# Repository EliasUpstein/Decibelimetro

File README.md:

# Decibelimetro
Proyecto anual integrador de la materia Medidas Electrónicas I - Ingeniería Electrónica - Universidad Tecnológica Nacional - Facultad Regional Buenos Aires

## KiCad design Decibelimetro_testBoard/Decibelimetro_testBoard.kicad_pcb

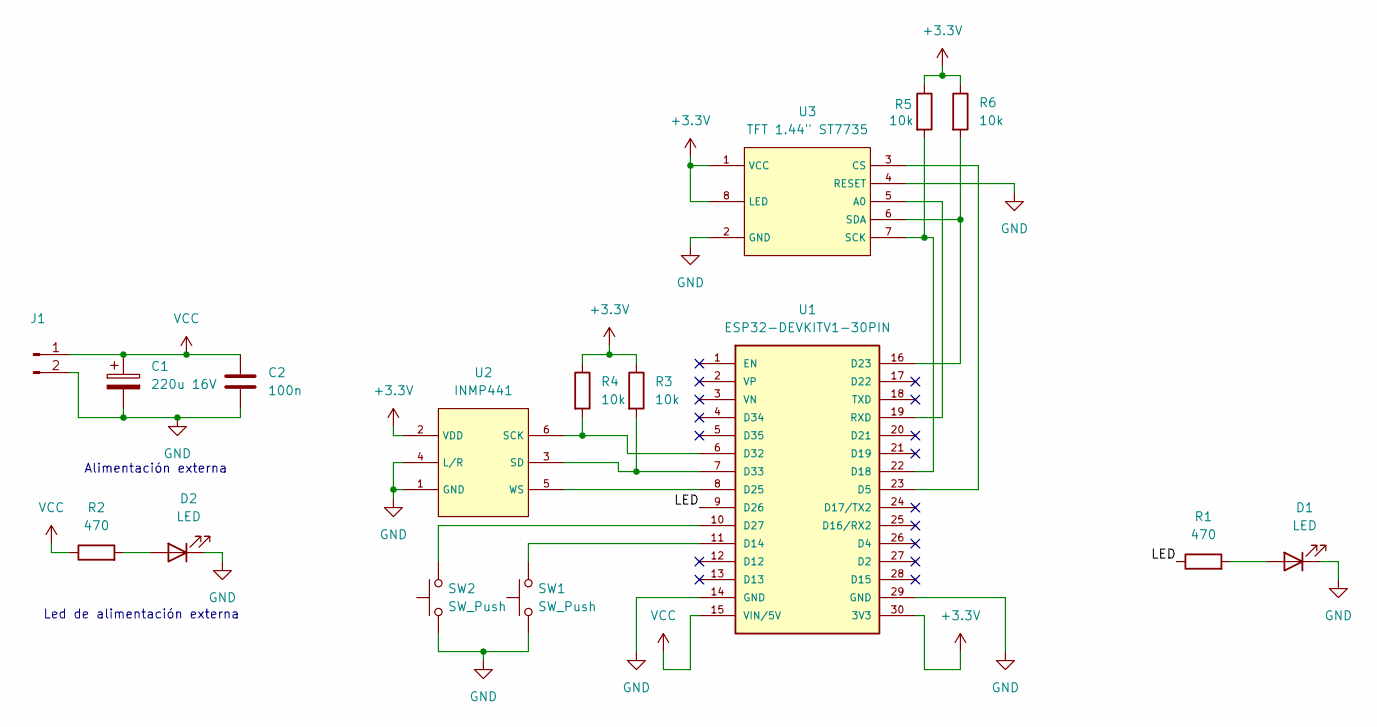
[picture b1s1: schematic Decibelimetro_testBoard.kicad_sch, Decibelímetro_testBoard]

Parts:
C1: 220u 16V; CP_Radial_D8.0mm_P3.80mm
C2: 100n; C_Disc_D5.0mm_W2.5mm_P5.00mm
D1, D2: LED; LED_D5.0mm
J1: Conn_01x02_Pin; TerminalBlock_bornier-2_P5.08mm
R1, R2: 470; R_Axial_DIN0207_L6.3mm_D2.5mm_P10.16mm_Horizontal
R3, R4, R5, R6: 10k; R_Axial_DIN0207_L6.3mm_D2.5mm_P10.16mm_Horizontal
SW1, SW2: SW_Push; SW_PUSH_6mm_H5mm
U1: ESP32-DEVKITV1-30PIN; ESP32-DEVKIT-30PIN; PARTREV V4
U2: INMP441
U3: TFT 1.44" ST7735; TFT 1.44_ ST7735

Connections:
+3.3V: R3.1, R4.1, R5.1, R6.1, U1.30 (3V3), U2.2 (VDD), U3.1 (VCC), U3.8 (LED)
/LED: R1.1, U1.9 (D26)
GND: C1.2, C2.2, D1.1 (K), D2.1 (K), J1.2, SW1.1, SW2.1, U1.14 (GND), U1.29 (GND), U2.1 (GND), U2.4 (L/R), U3.2 (GND), U3.4 (RESET)
unnamed: D1.2 (A), R1.2
unnamed: D2.2 (A), R2.2
unnamed: U1.23 (D5), U3.3 (CS)
unnamed: SW1.2, U1.11 (D14)
unnamed: R5.2, U1.22 (D18), U3.7 (SCK)
unnamed: R6.2, U1.16 (D23), U3.6 (SDA)
unnamed: U1.8 (D25), U2.5 (WS)
unnamed: SW2.2, U1.10 (D27)
unnamed: R4.2, U1.6 (D32), U2.6 (SCK)
unnamed: R3.2, U1.7 (D33), U2.3 (SD)
unnamed: U1.19 (RXD), U3.5 (A0)
VCC: C1.1, C2.1, J1.1, R2.1, U1.15 (VIN/5V)

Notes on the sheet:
Alimentación externa
Led de alimentación externa

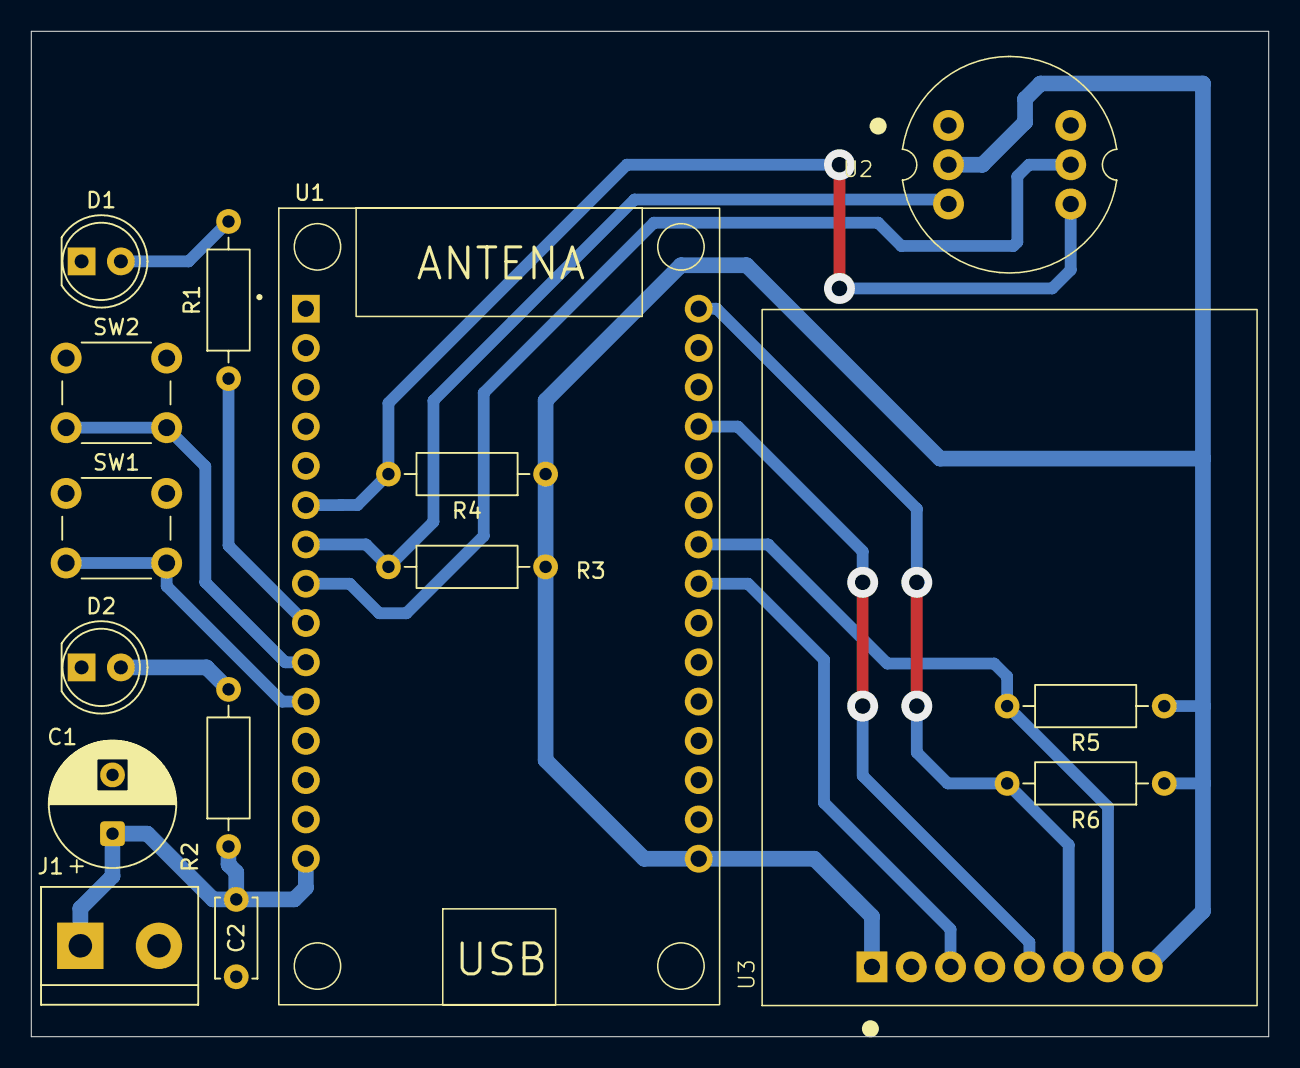
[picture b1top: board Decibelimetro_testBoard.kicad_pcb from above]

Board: 2 copper layers, 80.0 x 65.0 mm, 16 parts (0 on the bottom side), 15 nets.

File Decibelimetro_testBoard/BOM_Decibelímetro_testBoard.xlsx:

Qty | Value | Reference | Footprint
1 | 220u 16V | C1 | Capacitor_THT:CP_Radial_D8.0mm_P3.80mm
1 | 100n | C2 | Capacitor_THT:C_Disc_D5.0mm_W2.5mm_P5.00mm
2 | LED | D1,D2 | LED_THT:LED_D5.0mm
1 | Conn_01x02_Pin | J1 | TerminalBlock:TerminalBlock_bornier-2_P5.08mm
2 | 470 | R1,R2 | Resistor_THT:R_Axial_DIN0207_L6.3mm_D2.5mm_P10.16mm_Horizontal
4 | 10k | R3,R4,R5,R6 | Resistor_THT:R_Axial_DIN0207_L6.3mm_D2.5mm_P10.16mm_Horizontal
2 | SW_Push | SW1,SW2 | Button_Switch_THT:SW_PUSH_6mm_H5mm
1 | ESP32-DEVKITV1-30PIN | U1 | Decibelimetro_testBoard_librarie:ESP32-DEVKIT-30PIN
1 | INMP441 | U2 | Decibelimetro_testBoard_librarie:INMP441
1 | TFT 1.44" ST7735 | U3 | Decibelimetro_testBoard_librarie:TFT 1.44_ ST7735

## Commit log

2025-08-18 Inclusión de archivos base desarrollados por Mariano Pittaluga
2025-09-17 Decibelimetro-Patron: Manual y Programa
2025-09-22 Escritura/lectura Flash y envio de filtros por serial
2025-10-05 Cambios codigo, calculo de incertidumbre filtro A, eliminacion del filtro de compensacion
2025-10-21 Estado de calibracion
2025-10-24 Archivos de test
2025-10-29 Diseño de PCB de test
2025-12-14 Incorporo cambios de código sonometroV2
2025-12-14 Incorporo funcionalidad el led de umbral
